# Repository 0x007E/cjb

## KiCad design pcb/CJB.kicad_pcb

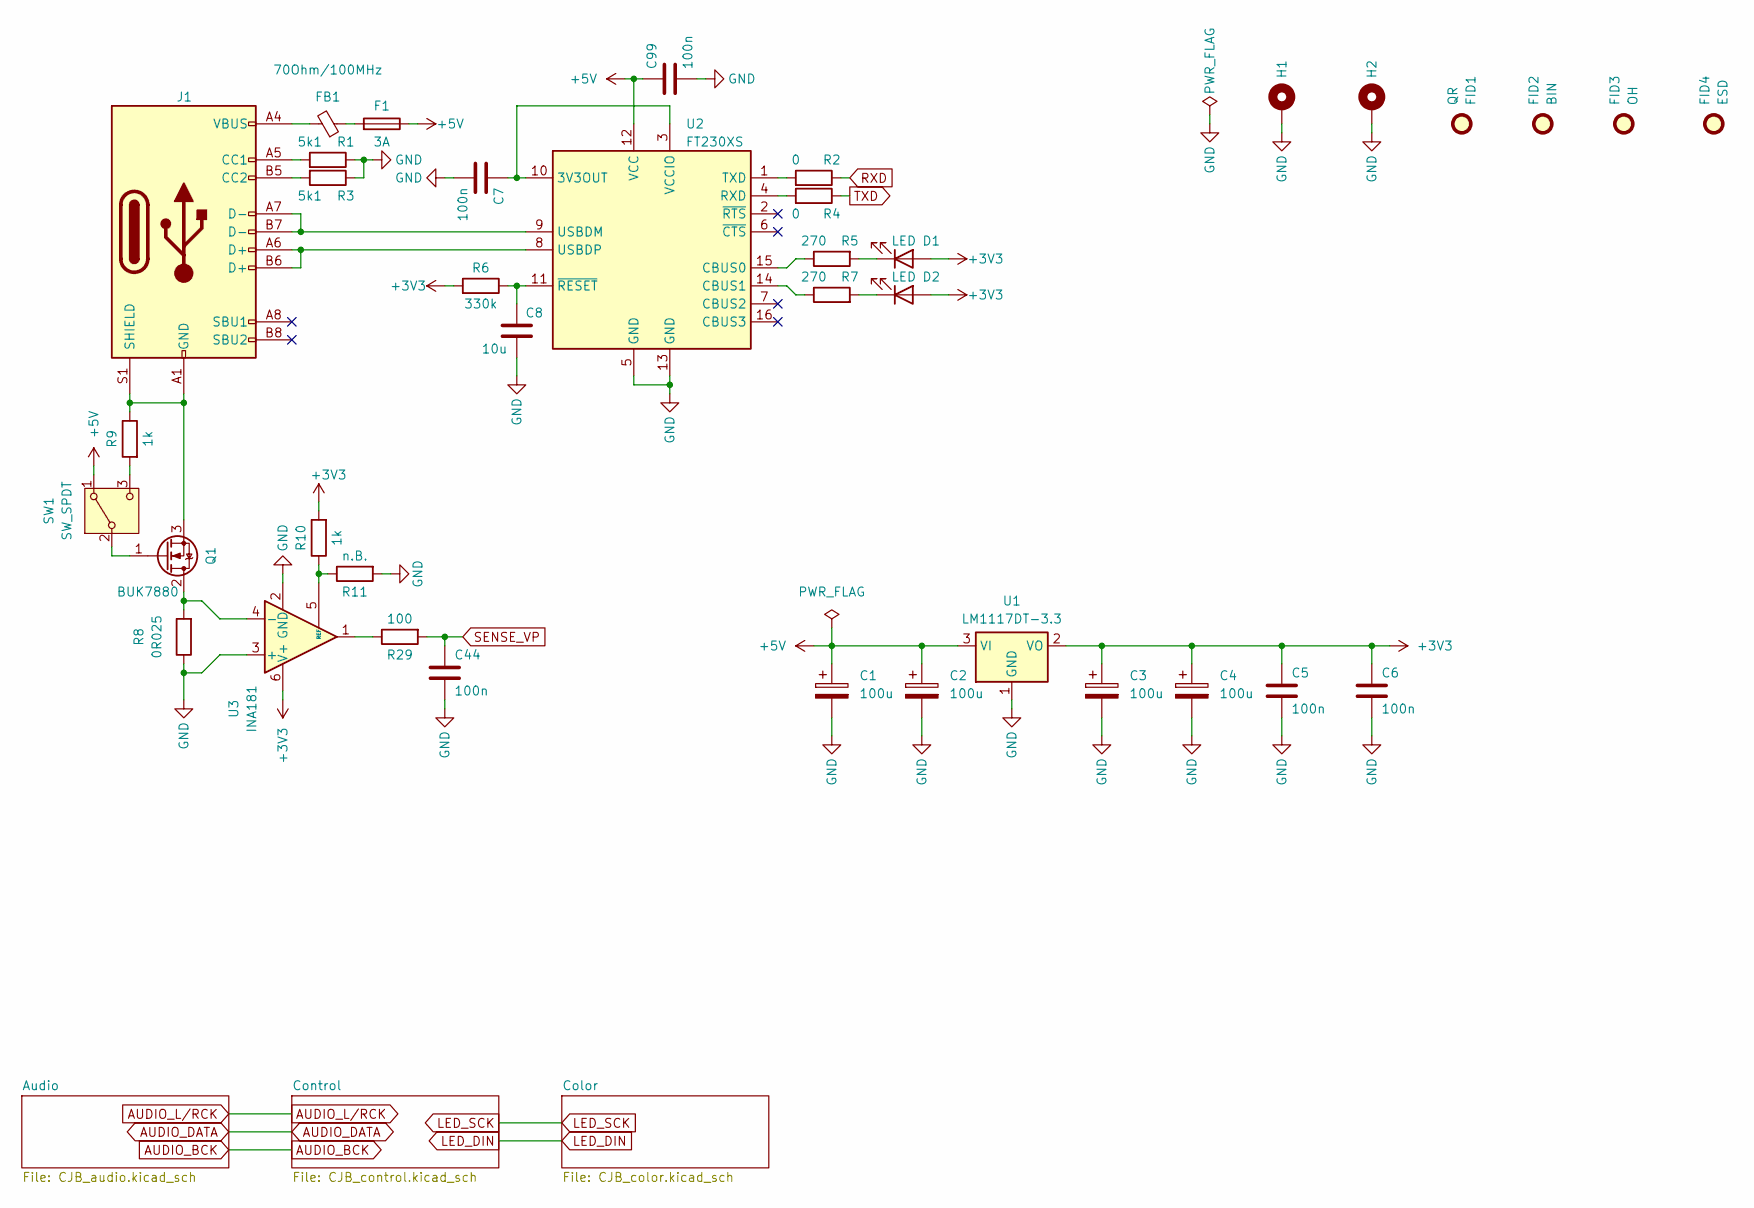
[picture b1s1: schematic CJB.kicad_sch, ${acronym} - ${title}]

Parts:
C1, C2, C3, C4: 100u; CP_Elec_6.3x5.2
C5, C6, C7, C44, C99: 100n; C_1206_3216Metric
C8: 10u; C_1206_3216Metric
D1, D2: LED; LED_1206_3216Metric
F1: 3A; Fuse_1206_3216Metric
FB1: 70Ohm/100MHz; L_1206_3216Metric
FID1: QR; QR_0x007e_small
FID2: BIN; WEEE-Logo_4.2x6mm_SilkScreen
FID3: OH; OSHW-Logo2_7.3x6mm_SilkScreen
FID4: ESD; ESD-Logo_6.6x6mm_SilkScreen
H1, H2: MountingHole_Pad; MountingHole_3.2mm_M3_DIN965_Pad
J1: USB_C_Receptacle_USB2.0_16P; USB_C_Receptacle_GCT_USB4110
Q1: BUK7880; SOT-223-3_TabPin2
R1, R3: 5k1; R_1206_3216Metric
R2, R4: 0; R_1206_3216Metric
R5, R7: 270; R_1206_3216Metric
R6: 330k; R_1206_3216Metric
R8: 0R025; R_2010_5025Metric
R9, R10: 1k; R_1206_3216Metric
R11: n.B.; R_1206_3216Metric
R29: 100; R_1206_3216Metric
SW1: SW_SPDT; PinHeader_1x03_P2.54mm_Vertical
U1: LM1117DT-3.3; TO-252-3_TabPin2
U2: FT230XS; SSOP-16_3.9x4.9mm_P0.635mm
U3: INA181; SOT-23-6

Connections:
+3V3: C3.1, C4.1, C5.2, C6.2, D1.2 (A), D2.2 (A), R6.2, R10.2, U1.2 (VO), U3.6 (V+); also elsewhere on the board
+5V: C1.1, C2.1, C99.2, F1.1, SW1.1 (A), U1.3 (VI), U2.12 (VCC); also elsewhere on the board
GND: C1.2, C2.2, C3.2, C4.2, C5.1, C6.1, C7.1, C8.1, C44.1, C99.1, H1.1, H2.1, R1.1, R3.1, R8.1, R11.2, U1.1 (GND), U2.5 (GND), U2.13 (GND), U3.2 (GND), U3.3 (+); also elsewhere on the board
unnamed: D1.1 (K), R5.2
unnamed: D2.1 (K), R7.2
unnamed: F1.2, FB1.1
unnamed: FB1.2, J1.A4 (VBUS), J1.A9 (VBUS), J1.B4 (VBUS), J1.B9 (VBUS)
unnamed: J1.A5 (CC1), R1.2
unnamed: J1.B5 (CC2), R3.2
unnamed: J1.A1 (GND), J1.A12 (GND), J1.B1 (GND), J1.B12 (GND), J1.S1 (SHIELD), Q1.3 (S), R9.1
unnamed: Q1.2 (D), R8.2, U3.4 (-)
unnamed: Q1.1 (G), SW1.2 (B)
unnamed: R29.1, U3.1
unnamed: R9.2, SW1.3 (C)
unnamed: C7.2, U2.3 (VCCIO), U2.10 (3V3OUT)
unnamed: R5.1, U2.15 (CBUS0)
unnamed: R7.1, U2.14 (CBUS1)
unnamed: R4.2, U2.4 (RXD)
unnamed: R2.2, U2.1 (TXD)
unnamed: J1.A7 (D-), J1.B7 (D-), U2.9 (USBDM)
unnamed: J1.A6 (D+), J1.B6 (D+), U2.8 (USBDP)
unnamed: C8.2, R6.1, U2.11 (~RESET)
unnamed: R10.1, R11.1, U3.5 (REF)
RXD: R2.1; also elsewhere on the board
SENSE_VP: C44.2, R29.2; also elsewhere on the board
TXD: R4.1; also elsewhere on the board

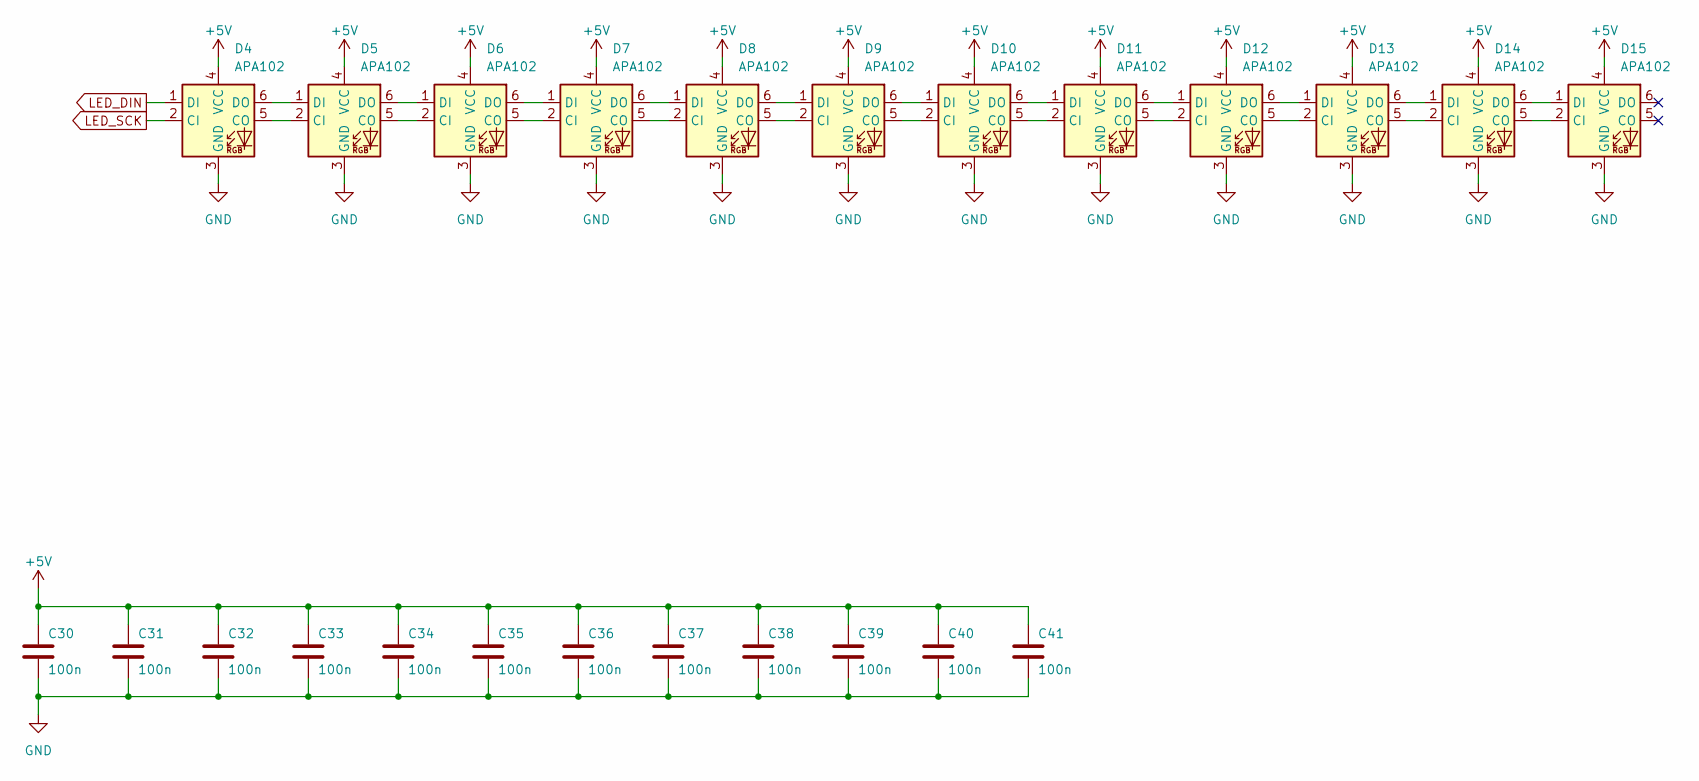
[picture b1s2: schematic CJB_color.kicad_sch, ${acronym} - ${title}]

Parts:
C30, C31, C32, C33, C34, C35, C36, C37, C38, C39, C40, C41: 100n; C_1206_3216Metric
D4, D5, D6, D7, D8, D9, D10, D11, D12, D13, D14, D15: APA102; LED_RGB_5050-6

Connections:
+5V: C30.2, C31.2, C32.2, C33.2, C34.2, C35.2, C36.2, C37.2, C38.2, C39.2, C40.2, C41.2, D4.4 (VCC), D5.4 (VCC), D6.4 (VCC), D7.4 (VCC), D8.4 (VCC), D9.4 (VCC), D10.4 (VCC), D11.4 (VCC), D12.4 (VCC), D13.4 (VCC), D14.4 (VCC), D15.4 (VCC); also elsewhere on the board
GND: C30.1, C31.1, C32.1, C33.1, C34.1, C35.1, C36.1, C37.1, C38.1, C39.1, C40.1, C41.1, D4.3 (GND), D5.3 (GND), D6.3 (GND), D7.3 (GND), D8.3 (GND), D9.3 (GND), D10.3 (GND), D11.3 (GND), D12.3 (GND), D13.3 (GND), D14.3 (GND), D15.3 (GND); also elsewhere on the board
LED_DIN: D4.1 (DI); also elsewhere on the board
LED_SCK: D4.2 (CI); also elsewhere on the board
unnamed: D4.5 (CO), D5.2 (CI)
unnamed: D4.6 (DO), D5.1 (DI)
unnamed: D5.5 (CO), D6.2 (CI)
unnamed: D5.6 (DO), D6.1 (DI)
unnamed: D6.5 (CO), D7.2 (CI)
unnamed: D6.6 (DO), D7.1 (DI)
unnamed: D7.5 (CO), D8.2 (CI)
unnamed: D7.6 (DO), D8.1 (DI)
unnamed: D8.5 (CO), D9.2 (CI)
unnamed: D8.6 (DO), D9.1 (DI)
unnamed: D9.5 (CO), D10.2 (CI)
unnamed: D10.5 (CO), D11.2 (CI)
unnamed: D9.6 (DO), D10.1 (DI)
unnamed: D10.6 (DO), D11.1 (DI)
unnamed: D11.5 (CO), D12.2 (CI)
unnamed: D11.6 (DO), D12.1 (DI)
unnamed: D12.5 (CO), D13.2 (CI)
unnamed: D12.6 (DO), D13.1 (DI)
unnamed: D13.5 (CO), D14.2 (CI)
unnamed: D13.6 (DO), D14.1 (DI)
unnamed: D14.5 (CO), D15.2 (CI)
unnamed: D14.6 (DO), D15.1 (DI)

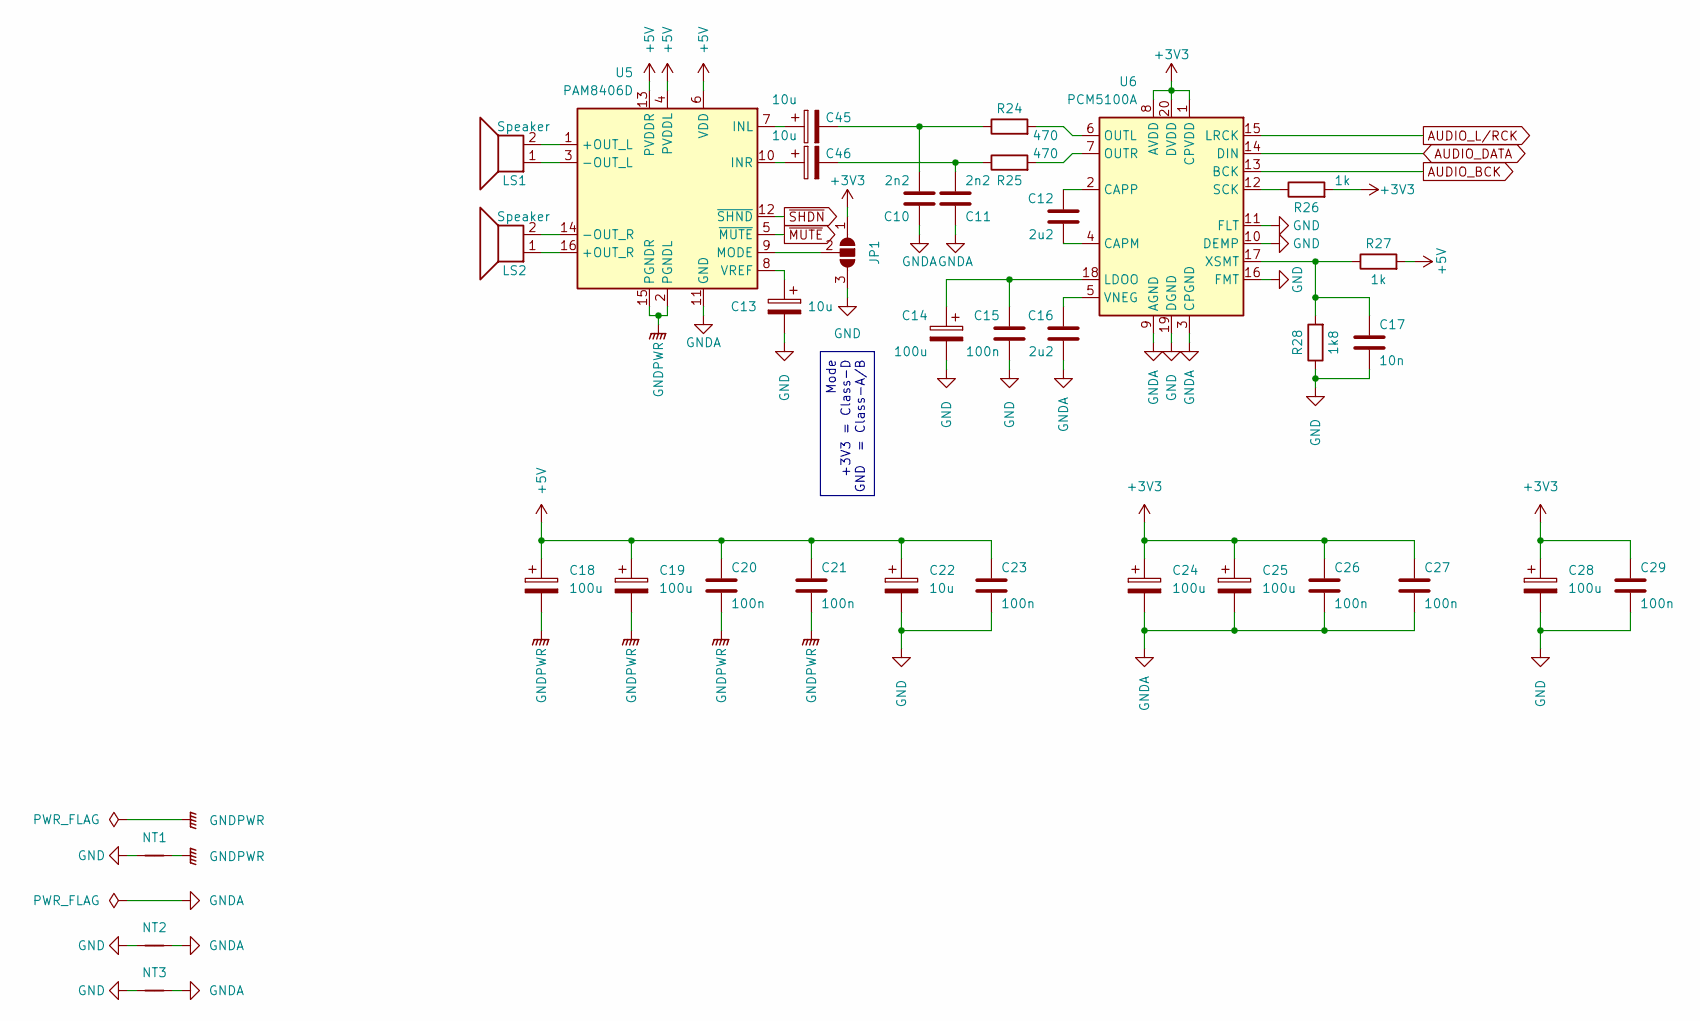
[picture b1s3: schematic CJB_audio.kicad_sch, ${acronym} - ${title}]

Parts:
C10, C11: 2n2; C_1206_3216Metric
C12, C16: 2u2; C_1206_3216Metric
C13, C22, C45, C46: 10u; CP_Elec_5x5.3
C14, C18, C19, C24, C25, C28: 100u; CP_Elec_6.3x5.2
C15, C20, C21, C23, C26, C27, C29: 100n; C_1206_3216Metric
C17: 10n; C_1206_3216Metric
JP1: SolderJumper_3_Open; SolderJumper-3_P1.3mm_Open_Pad1.0x1.5mm_NumberLabels
LS1, LS2: Speaker; TerminalBlock_Phoenix_MKDS-1,5-2-5.08_1x02_P5.08mm_Horizont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
NT1, NT2, NT3: NetTie_2; NetTie-2_SMD_Pad2.0mm
R24, R25: 470; R_1206_3216Metric
R26, R27: 1k; R_1206_3216Metric
R28: 1k8; R_1206_3216Metric
U5: PAM8406D; SOIC-16_3.9x9.9mm_P1.27mm
U6: PCM5100A; TSSOP-20_4.4x6.5mm_P0.65mm

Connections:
+3V3: C24.1, C25.1, C26.2, C27.2, C28.1, C29.2, JP1.1 (A), R26.2, U6.1 (CPVDD), U6.8 (AVDD), U6.20 (DVDD); also elsewhere on the board
+5V: C18.1, C19.1, C20.2, C21.2, C22.1, C23.2, R27.2, U5.4 (PVDDL), U5.6 (VDD), U5.13 (PVDDR); also elsewhere on the board
AUDIO_BCK: U6.13 (BCK); also elsewhere on the board
AUDIO_DATA: U6.14 (DIN); also elsewhere on the board
AUDIO_L/RCK: U6.15 (LRCK); also elsewhere on the board
GND: C13.2, C14.2, C15.1, C17.1, C22.2, C23.1, C28.2, C29.1, JP1.3 (B), NT1.1, NT2.1, NT3.1, R28.1, U6.10 (DEMP), U6.11 (FLT), U6.16 (FMT), U6.19 (DGND); also elsewhere on the board
GNDA: C10.2, C11.2, C16.1, C24.2, C25.2, C26.1, C27.1, NT2.2, NT3.2, U5.11 (GND), U6.3 (CPGND), U6.9 (AGND)
GNDPWR: C18.2, C19.2, C20.1, C21.1, NT1.2, U5.2 (PGNDL), U5.15 (PGNDR)
unnamed: C10.1, C45.2, R24.1
unnamed: C11.1, C46.2, R25.1
unnamed: JP1.2 (C), U5.9 (MODE)
unnamed: LS1.2, U5.1 (+OUT_L)
unnamed: LS2.1, U5.16 (+OUT_R)
unnamed: LS1.1, U5.3 (-OUT_L)
unnamed: LS2.2, U5.14 (-OUT_R)
unnamed: C45.1, U5.7 (INL)
unnamed: C46.1, U5.10 (INR)
unnamed: C13.1, U5.8 (VREF)
unnamed: C12.1, U6.4 (CAPM)
unnamed: C12.2, U6.2 (CAPP)
unnamed: C14.1, C15.2, U6.18 (LDOO)
unnamed: R24.2, U6.6 (OUTL)
unnamed: R25.2, U6.7 (OUTR)
unnamed: R26.1, U6.12 (SCK)
unnamed: C16.2, U6.5 (VNEG)
unnamed: C17.2, R27.1, R28.2, U6.17 (XSMT)
~MUTE: U5.5 (~MUTE); also elsewhere on the board
~SHDN: U5.12 (~SHND); also elsewhere on the board

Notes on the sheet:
Mode +3V3 = Class-D GND = Class-A/B

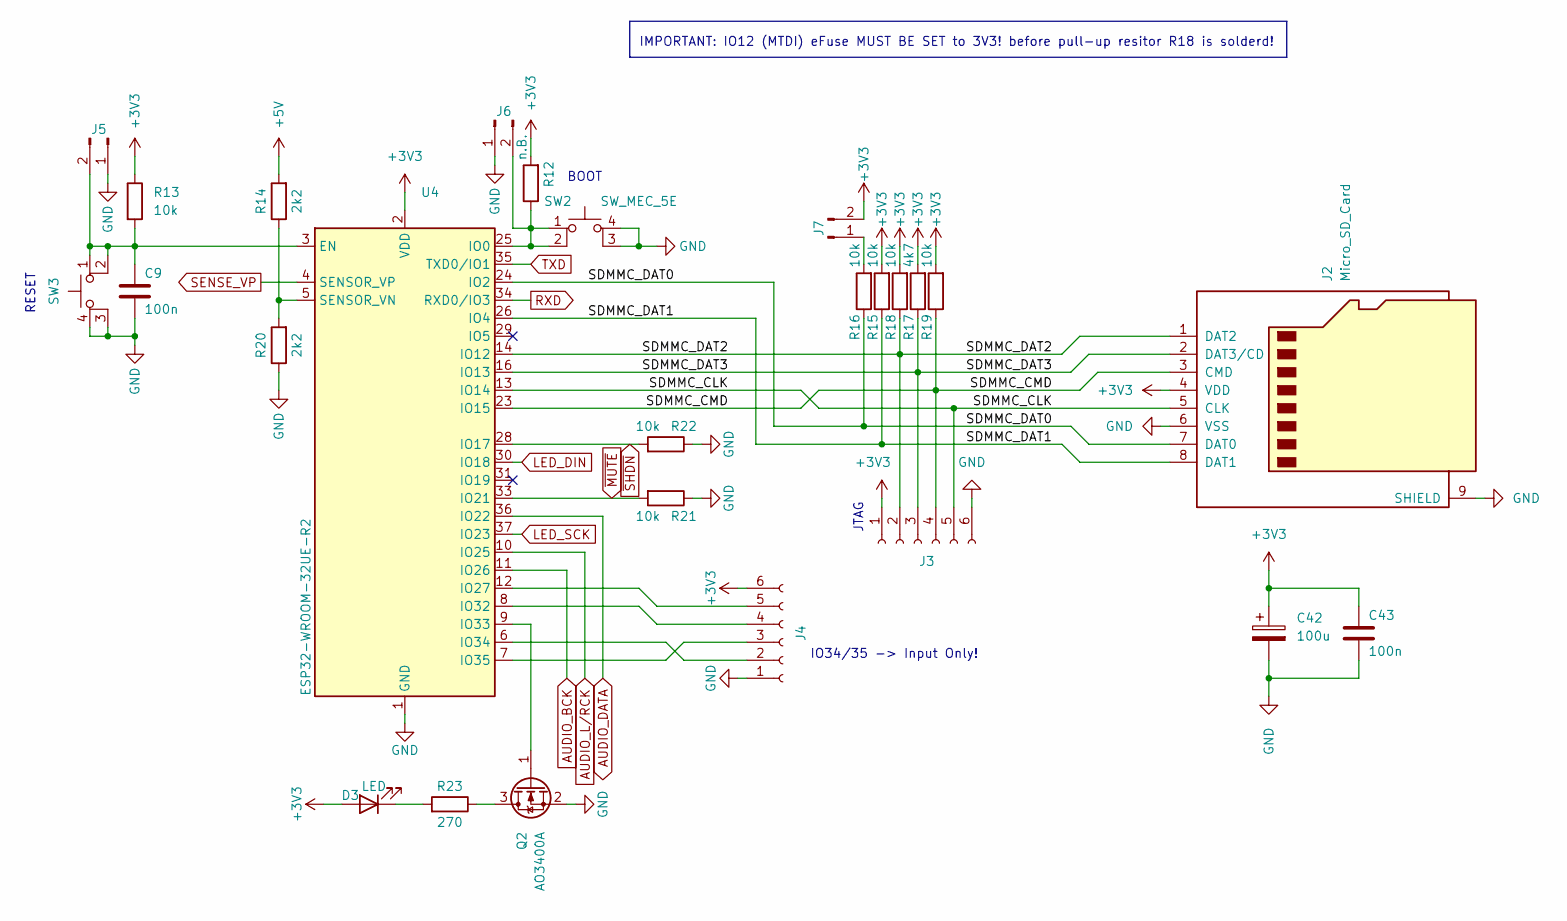
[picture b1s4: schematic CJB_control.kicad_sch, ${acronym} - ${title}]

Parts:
C9, C43: 100n; C_1206_3216Metric
C42: 100u; CP_Elec_6.3x5.2
D3: LED; LED_1206_3216Metric
J2: Micro_SD_Card; microSD_HC_Molex_47219-2001
J3, J4: Conn_01x06_Socket; PinSocket_1x06_P2.54mm_Vertical
J5, J6, J7: Conn_01x02_Pin; PinHeader_1x02_P2.54mm_Vertical
Q2: AO3400A; SOT-23
R12: n.B.; R_1206_3216Metric
R13, R15, R16, R18, R19, R21, R22: 10k; R_1206_3216Metric
R14, R20: 2k2; R_1206_3216Metric
R17: 4k7; R_1206_3216Metric
R23: 270; R_1206_3216Metric
SW2, SW3: SW_MEC_5E; SW_PTS530_GK055_SMTR_LFS
U4: ESP32-WROOM-32UE-R2; ESP32-WROOM-32U

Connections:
+3V3: C42.1, C43.2, D3.2 (A), J2.4 (VDD), J3.1, J4.6, J7.2, R12.2, R13.1, R15.2, R17.2, R18.2, R19.2, U4.2 (VDD); also elsewhere on the board
+5V: R14.2; also elsewhere on the board
/Control/SDMMC_CLK: J2.5 (CLK), J3.5, U4.13 (IO14)
/Control/SDMMC_CMD: J2.3 (CMD), J3.4, R19.1, U4.23 (IO15)
/Control/SDMMC_DAT0: J2.7 (DAT0), R16.1, U4.24 (IO2)
/Control/SDMMC_DAT1: J2.8 (DAT1), R15.1, U4.26 (IO4)
/Control/SDMMC_DAT2: J2.1 (DAT2), J3.2, R18.1, U4.14 (IO12)
/Control/SDMMC_DAT3: J2.2 (DAT3/CD), J3.3, R17.1, U4.16 (IO13)
AUDIO_BCK: U4.11 (IO26); also elsewhere on the board
AUDIO_DATA: U4.36 (IO22); also elsewhere on the board
AUDIO_L/RCK: U4.10 (IO25); also elsewhere on the board
GND: C9.1, C42.2, C43.1, J2.6 (VSS), J2.9 (SHIELD), J3.6, J4.1, J5.1, J6.1, Q2.2 (S), R20.1, R21.1, R22.1, SW2.3 (K), SW2.4 (A), SW3.3 (K), SW3.4 (A), U4.1 (GND), U4.15 (GND), U4.38 (GND), U4.39 (GND); also elsewhere on the board
LED_DIN: U4.30 (IO18); also elsewhere on the board
LED_SCK: U4.37 (IO23); also elsewhere on the board
unnamed: D3.1 (K), R23.2
unnamed: J4.2, U4.6 (IO34)
unnamed: J4.3, U4.7 (IO35)
unnamed: J4.4, U4.8 (IO32)
unnamed: J4.5, U4.12 (IO27)
unnamed: C9.2, J5.2, R13.2, SW3.1, SW3.2, U4.3 (EN)
unnamed: J6.2, R12.1, SW2.1, SW2.2, U4.25 (IO0)
unnamed: J7.1, R16.2
unnamed: Q2.3 (D), R23.1
unnamed: Q2.1 (G), U4.9 (IO33)
unnamed: R14.1, R20.2, U4.5 (SENSOR_VN)
RXD: U4.34 (RXD0/IO3); also elsewhere on the board
SENSE_VP: U4.4 (SENSOR_VP); also elsewhere on the board
TXD: U4.35 (TXD0/IO1); also elsewhere on the board
~MUTE: R21.2, U4.33 (IO21); also elsewhere on the board
~SHDN: R22.2, U4.28 (IO17); also elsewhere on the board

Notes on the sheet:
BOOT
IO34/35 -> Input Only!
RESET
JTAG
IMPORTANT: IO12 (MTDI) eFuse MUST BE SET to 3V3! before pull-up resitor R18 is solderd!

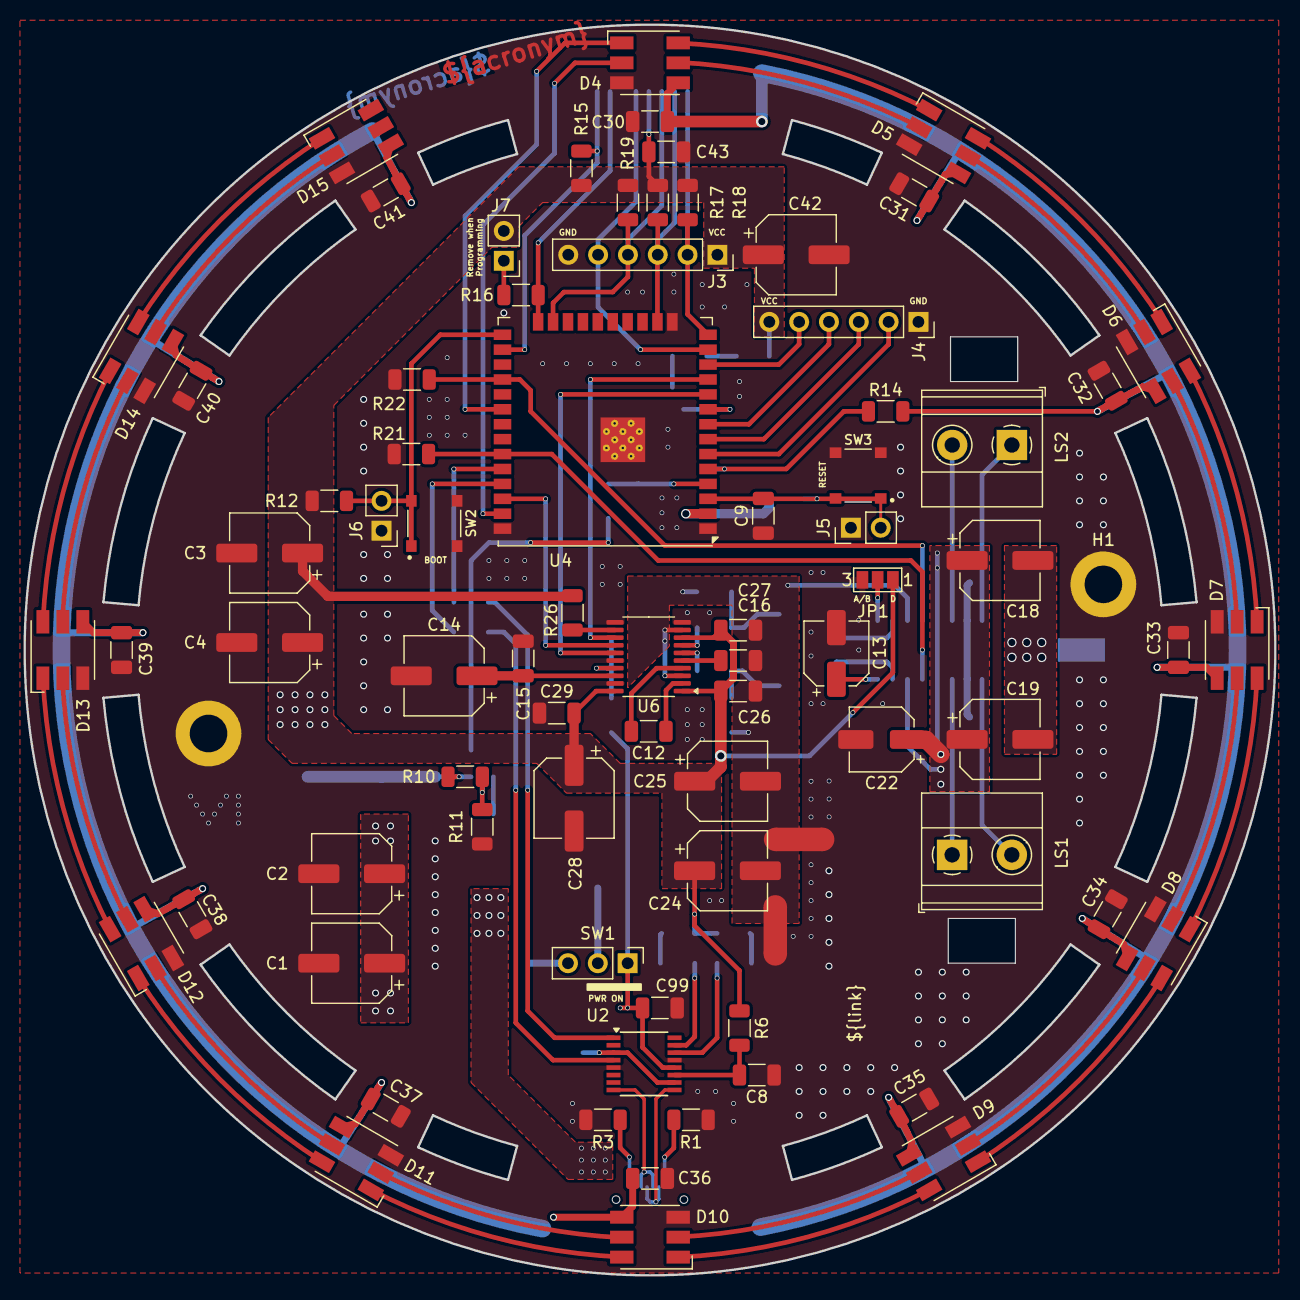
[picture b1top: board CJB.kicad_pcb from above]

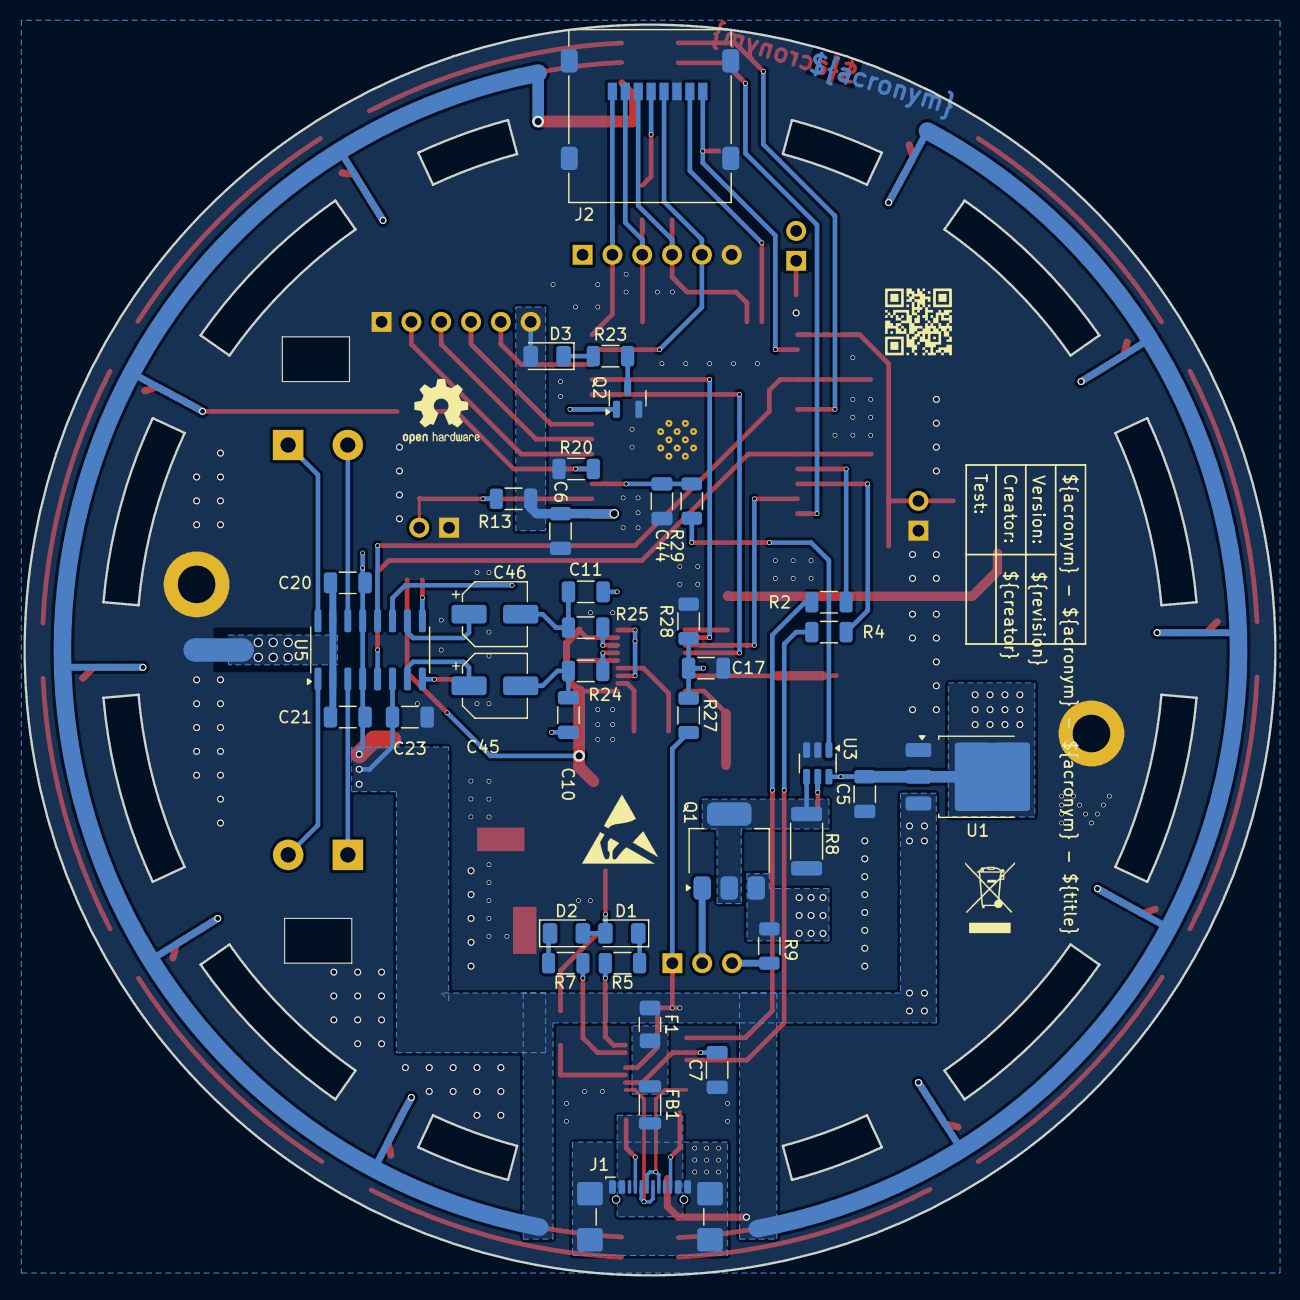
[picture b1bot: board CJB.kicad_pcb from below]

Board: 2 copper layers, 106.5 x 106.5 mm, 123 parts (43 on the bottom side), 92 nets.

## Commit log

2026-02-20 Add pcb layout
2026-03-04 Add build pipeline
2026-03-04 Fix fabrication layer positions
2026-03-04 Fix wrong vendor id
2026-03-12 Change uart resistor values
2026-03-16 Add BOOT and RESET jumper
2026-03-27 Fix boot and power issue
2026-03-27 Change SHDN and MUTE pins
2026-03-27 Modify pcb position
2026-03-27 Optimize silkscreen text
2026-04-01 Add dimensioning
2026-04-01 Add mechanical parts
2026-04-01 Change env variables to upper case
2026-04-01 Add FreeCAD job
2026-04-08 Rename apa102 spi clk/data pins
2026-04-09 Reduce diameter of speaker plate
2026-04-10 Adapt acrylglass screw hole diameter
2026-04-10 Adapt mounting screw position of acrylglass and outer ring

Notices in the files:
parts and their libraries:
license: CC BY-NC-SA 4.0
